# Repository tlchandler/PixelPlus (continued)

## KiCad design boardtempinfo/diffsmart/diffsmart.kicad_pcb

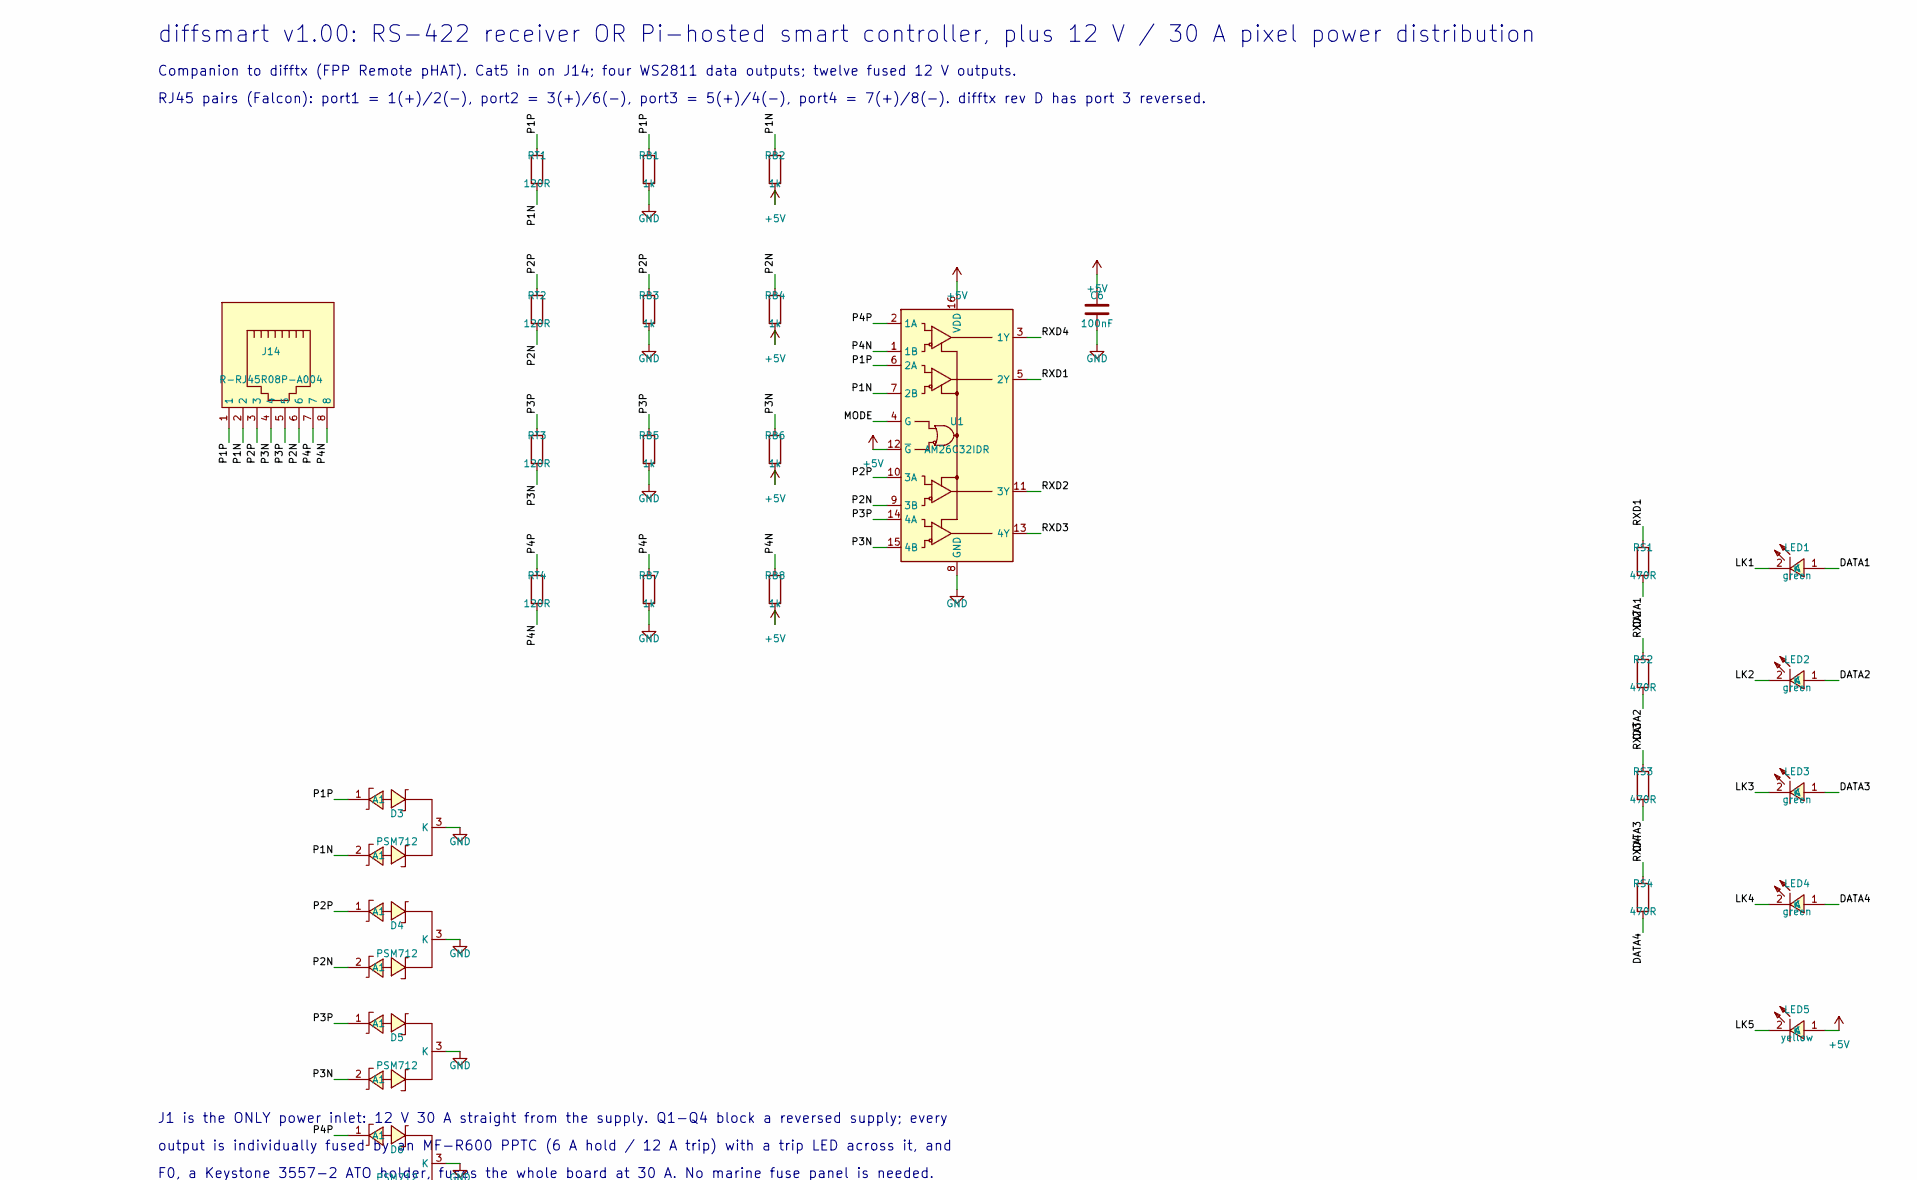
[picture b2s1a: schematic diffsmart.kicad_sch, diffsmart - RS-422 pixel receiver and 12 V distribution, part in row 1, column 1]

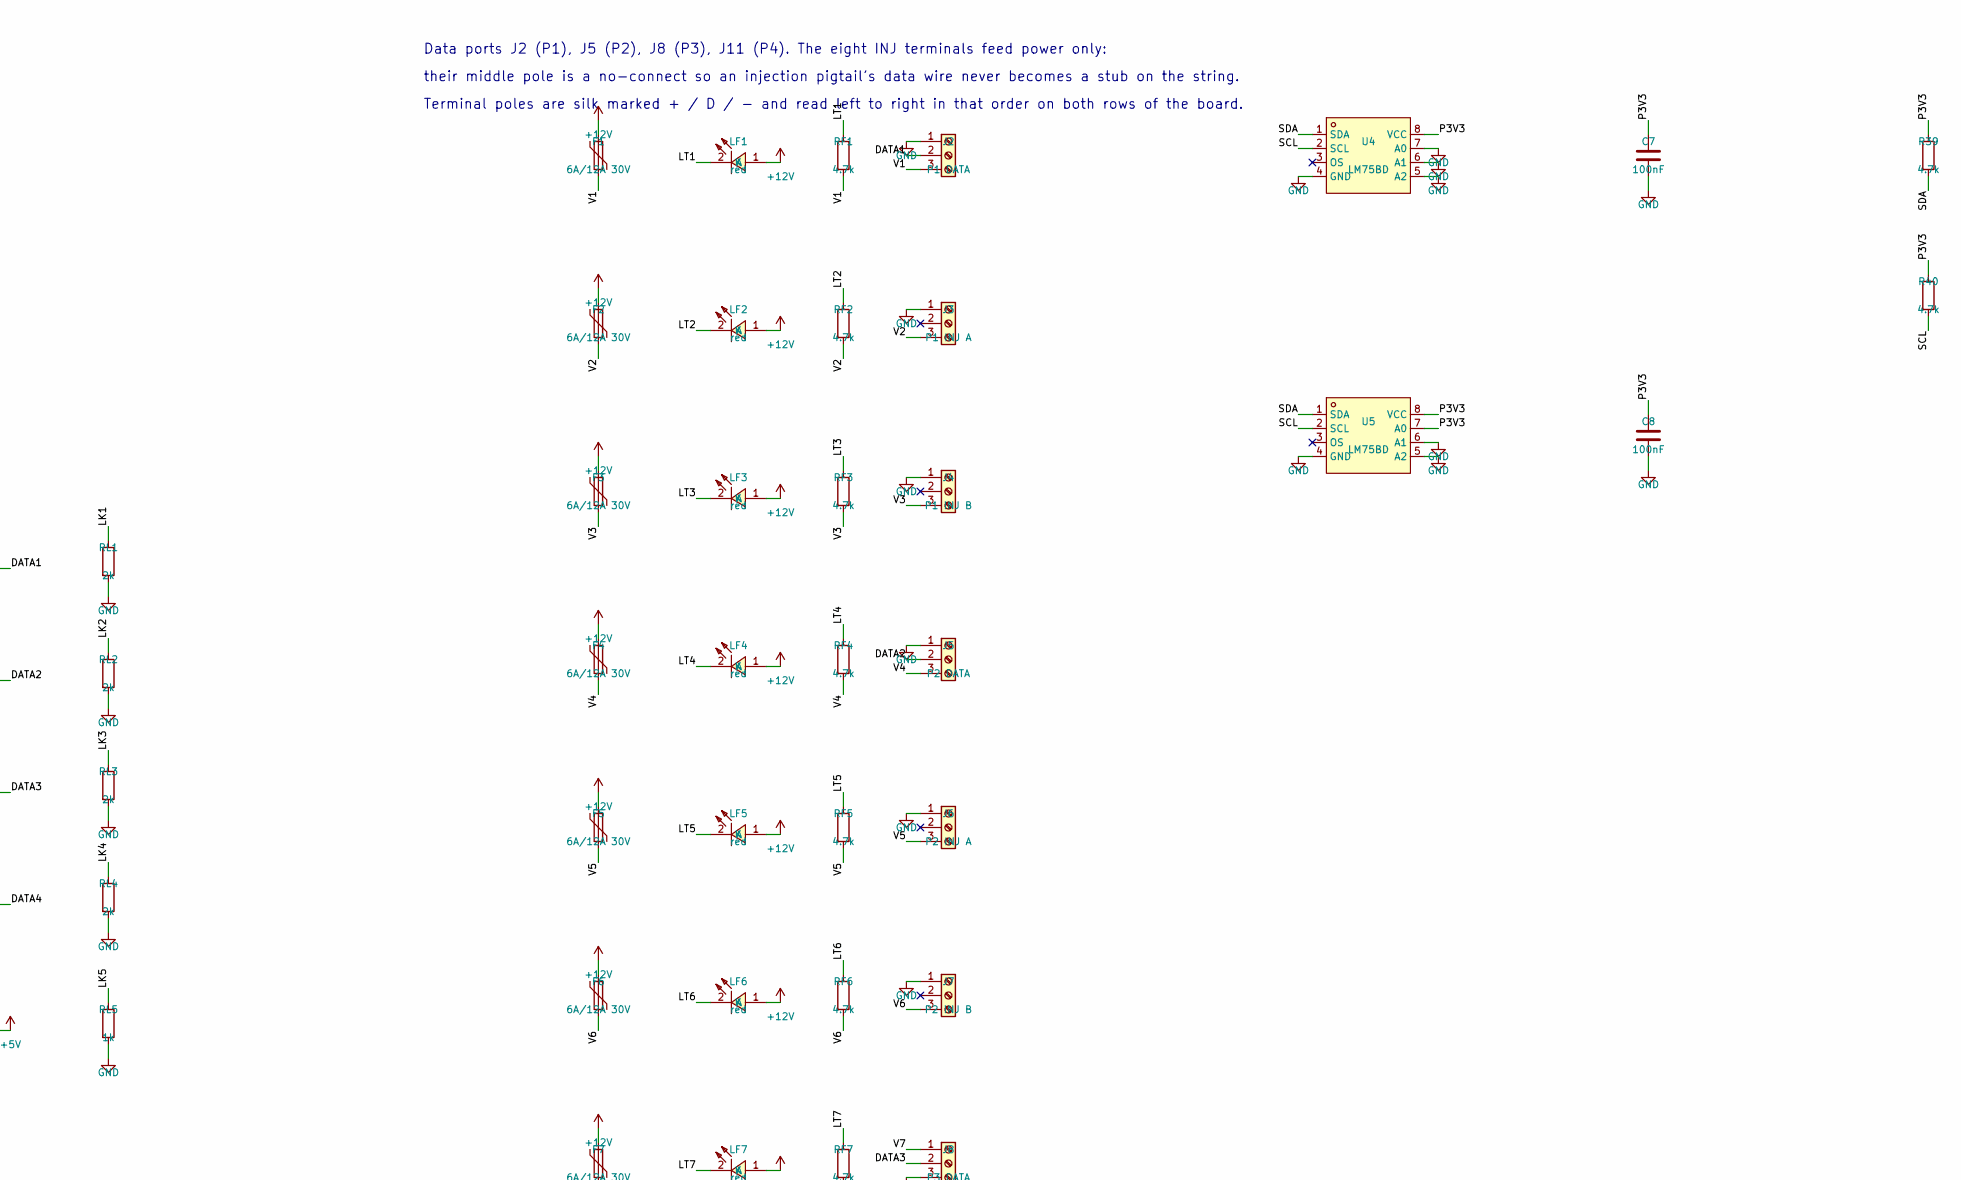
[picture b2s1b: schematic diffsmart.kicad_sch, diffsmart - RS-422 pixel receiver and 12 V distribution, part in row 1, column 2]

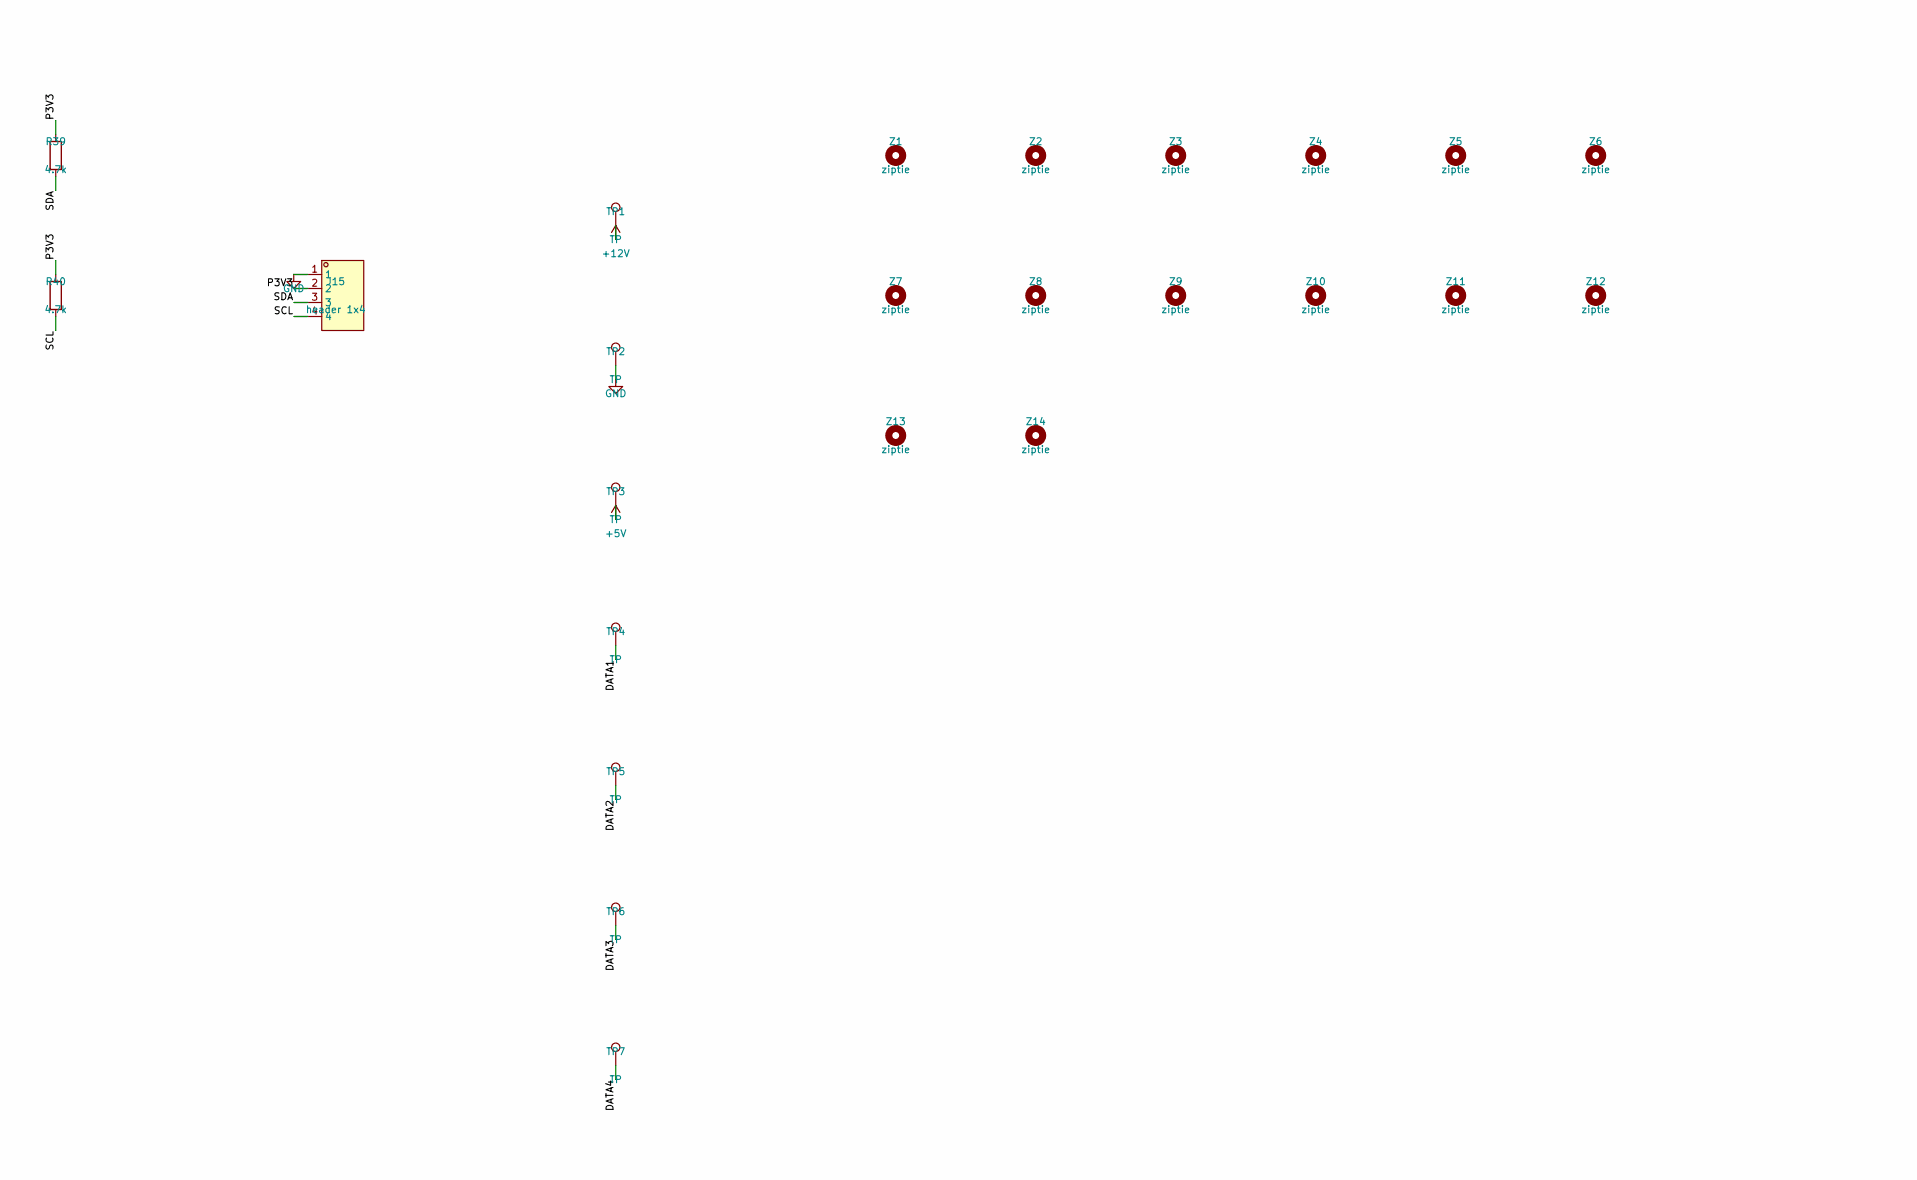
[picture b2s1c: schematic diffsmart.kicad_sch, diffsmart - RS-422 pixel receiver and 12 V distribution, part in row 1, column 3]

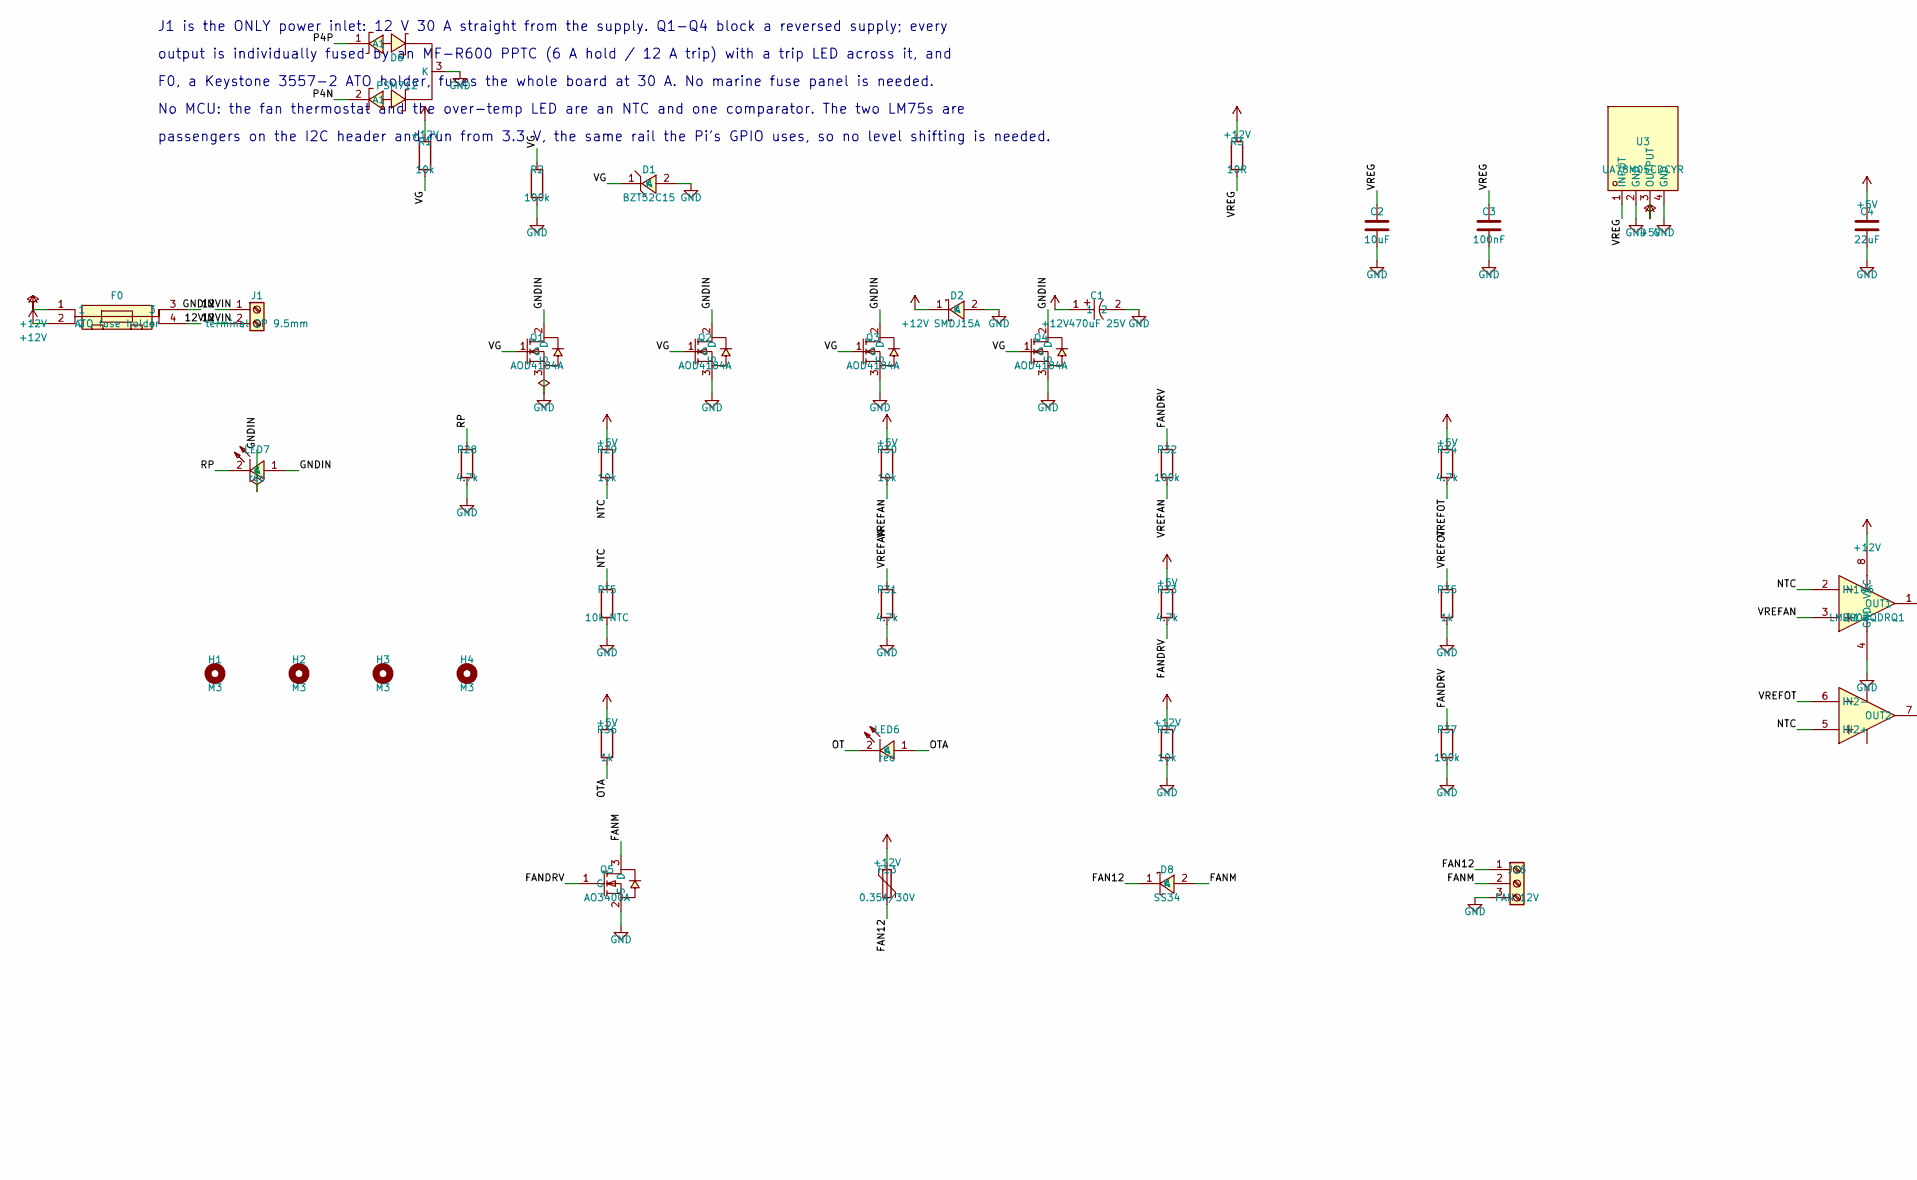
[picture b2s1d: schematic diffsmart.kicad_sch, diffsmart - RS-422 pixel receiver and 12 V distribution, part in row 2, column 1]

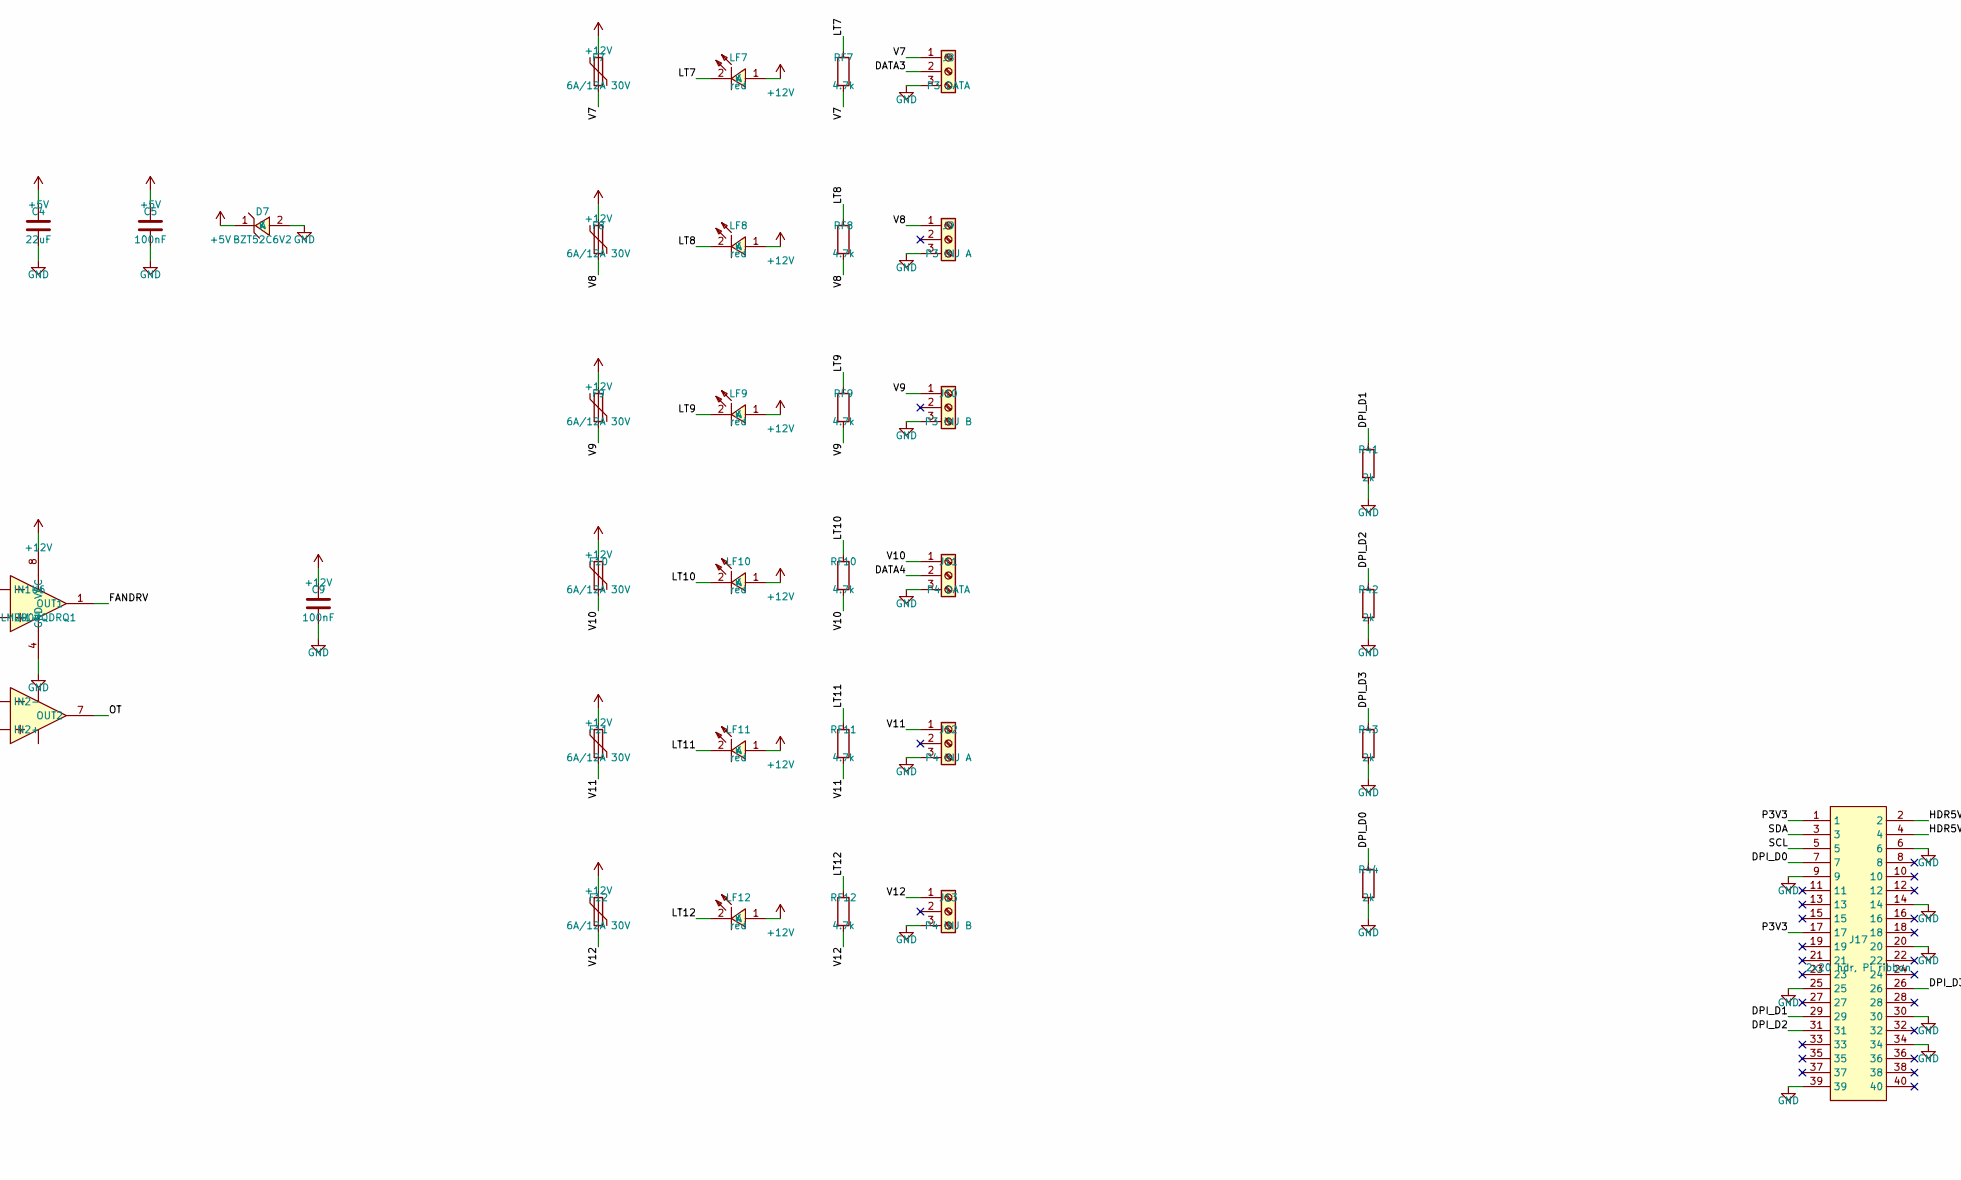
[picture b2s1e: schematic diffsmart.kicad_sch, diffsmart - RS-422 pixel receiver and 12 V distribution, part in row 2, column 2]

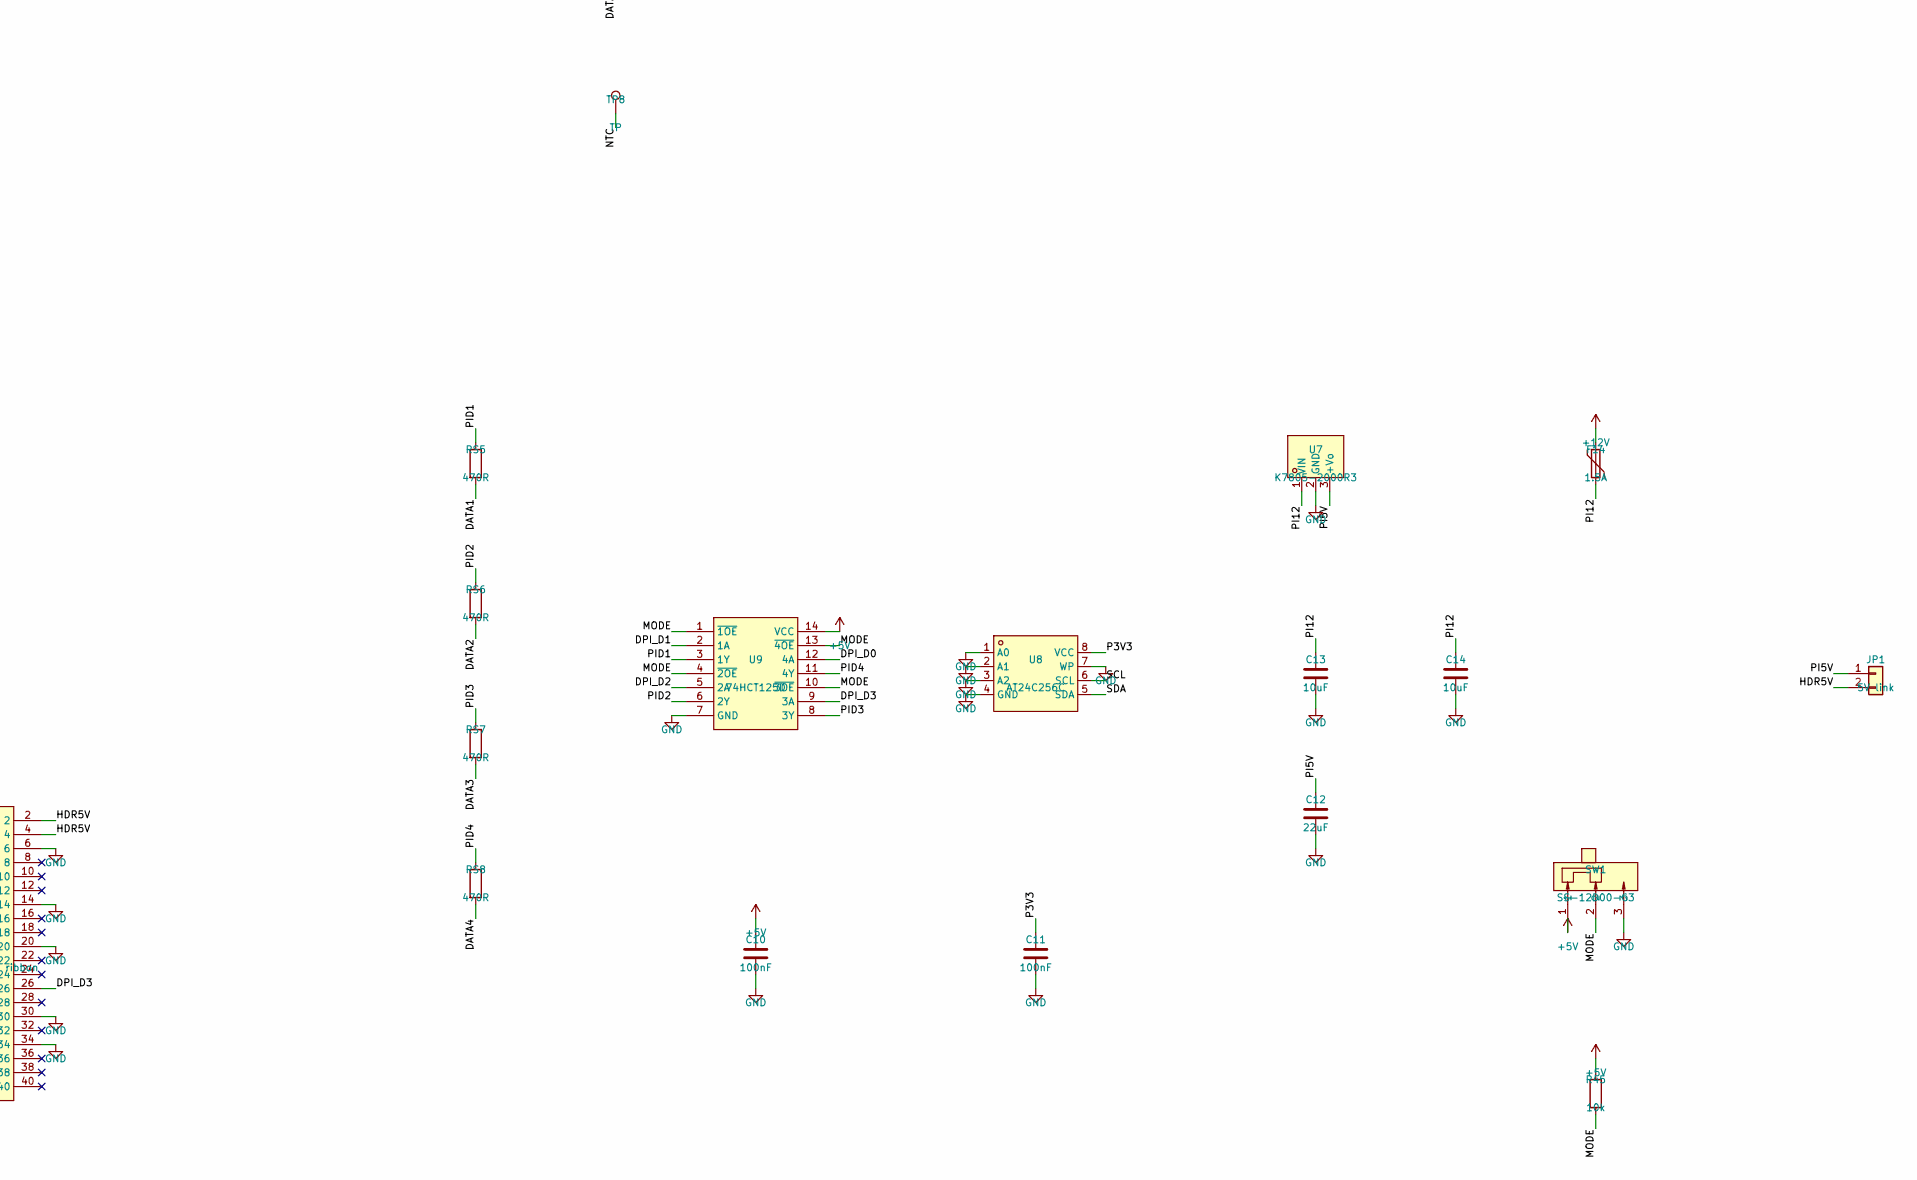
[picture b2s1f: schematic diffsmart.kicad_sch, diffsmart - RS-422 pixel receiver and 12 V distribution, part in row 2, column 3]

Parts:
C1: 470uF 25V; CAP-SMD_BD8.0-L8.3-W8.3-FD; LCSC C4747956
C2, C13, C14: 10uF; C_1206_3216Metric; LCSC C13585
C3, C5, C6, C7, C8, C9, C10, C11: 100nF; C_0805_2012Metric_Pad1.18x1.45mm_HandSolder; LCSC C49678
C4, C12: 22uF; C_0805_2012Metric_Pad1.18x1.45mm_HandSolder; LCSC C45783
D1: BZT52C15; SOD-123_L2.8-W1.8-LS3.7-RD; LCSC C2104
D2: SMDJ15A; SMC_L6.9-W5.9-LS7.9-RD; LCSC C152077
D3, D4, D5, D6: PSM712; SOT-23-3_L3.0-W1.7-P0.95-LS2.9-BR; LCSC C32677
D7: BZT52C6V2; SOD-123_L2.8-W1.8-LS3.7-RD; LCSC C173405
D8: SS34; SMA_L4.3-W2.6-LS5.2-RD; LCSC C8678
F0: ATO fuse holder; FUSE-TH_4P-L19.8-W6.7_3557-2; LCSC C352820
F1, F2, F3, F4, F5, F6, F7, F8, F9, F10, F11, F12: 6A/12A 30V; FUSE-TH_L19.1-W3.0-P10.20-D1.2-S2.0; LCSC C208490
F13: 0.35A/30V; Fuse_1206_3216Metric; LCSC C2876002
F14: 1.5A; F1812; LCSC C22392774
H1, H2, H3, H4: M3; MountingHole_3.2mm_M3
J1: terminal 2P 9.5mm; CONN-TH_P9.50_KF950-9.5-2P; LCSC C475106
J2: P1 DATA; CONN-TH_3P-P5.00_KF301-5.0-3P; LCSC C474882
J3: P1 INJ A; CONN-TH_3P-P5.00_KF301-5.0-3P; LCSC C474882
J4: P1 INJ B; CONN-TH_3P-P5.00_KF301-5.0-3P; LCSC C474882
J5: P2 DATA; CONN-TH_3P-P5.00_KF301-5.0-3P; LCSC C474882
J6: P2 INJ A; CONN-TH_3P-P5.00_KF301-5.0-3P; LCSC C474882
J7: P2 INJ B; CONN-TH_3P-P5.00_KF301-5.0-3P; LCSC C474882
J8: P3 DATA; CONN-TH_3P-P5.00_KF301-5.0-3P; LCSC C474882
J9: P3 INJ A; CONN-TH_3P-P5.00_KF301-5.0-3P; LCSC C474882
J10: P3 INJ B; CONN-TH_3P-P5.00_KF301-5.0-3P; LCSC C474882
J11: P4 DATA; CONN-TH_3P-P5.00_KF301-5.0-3P; LCSC C474882
J12: P4 INJ A; CONN-TH_3P-P5.00_KF301-5.0-3P; LCSC C474882
J13: P4 INJ B; CONN-TH_3P-P5.00_KF301-5.0-3P; LCSC C474882
J14: R-RJ45R08P-A004; RJ45-TH_R-RJ45R08P-A004; LCSC C385834
J15: header 1x4; HDR-TH_4P-P2.54-V-M; LCSC C124378
J16: FAN 12V; CONN-TH_3P-P5.00_KF301-5.0-3P; LCSC C474882
J17: 2x20 hdr, Pi ribbon; PiRibbon_2x20_P2.54mm; LCSC C50980
JP1: 5V link; PinHeader_1x02_P2.54mm_Vertical; LCSC C124375
LED1, LED2, LED3, LED4: green; LED0805-R-RD; LCSC C2297
LED5: yellow; LED0805-R-RD; LCSC C2296
LED6, LED7: red; LED0805-R-RD; LCSC C2295
LF1, LF2, LF3, LF4, LF5, LF6, LF7, LF8, LF9, LF10, LF11, LF12: red; LED0805-R-RD; LCSC C2295
Q1, Q2, Q3, Q4: AOD4184A; TO-252-2_L6.6-W6.1-P4.57-LS9.9-TL-CW; LCSC C99124
Q5: AO3400A; SOT-23-3_L2.9-W1.3-P1.90-LS2.4-BR; LCSC C20917
R1, R27, R29, R30, R45: 10k; R_0603_1608Metric; LCSC C25804
R2, R32, R37: 100k; R_0603_1608Metric; LCSC C25803
R3: 10R; R_0603_1608Metric; LCSC C22859
R28, R31, R33, R34, R39, R40: 4.7k; R_0603_1608Metric; LCSC C23162
R35, R36: 1k; R_0603_1608Metric; LCSC C21190
R41, R42, R43, R44: 2k; R_0603_1608Metric; LCSC C22975
RB1, RB2, RB3, RB4, RB5, RB6, RB7, RB8: 1k; R_0603_1608Metric; LCSC C21190
RF1, RF2, RF3, RF4, RF5, RF6, RF7, RF8, RF9, RF10, RF11, RF12: 4.7k; R_0603_1608Metric; LCSC C23162
RL1, RL2, RL3, RL4: 2k; R_0603_1608Metric; LCSC C22975
RL5: 1k; R_0603_1608Metric; LCSC C21190
RS1, RS2, RS3, RS4, RS5, RS6, RS7, RS8: 470R; R_0603_1608Metric; LCSC C23179
RT1, RT2, RT3, RT4: 120R; R_1206_3216Metric; LCSC C17909
RT5: 10k NTC; R_0805_2012Metric; LCSC C3195213
SW1: SS-12D00-G3; SW-TH_3P-L8.8-W3.9-P2.50_SS12D00G3; LCSC C22355741
TP1, TP2, TP3, TP4, TP5, TP6, TP7, TP8: TP; TestPoint_Pad_D1.5mm
U1: AM26C32IDR; SOIC-16_L9.9-W3.9-P1.27-LS6.0-BL; LCSC C36693
U3: UA78M05CDCYR; SOT-223_L6.5-W3.5-P2.30-LS7.0-BR; LCSC C201654
U4, U5: LM75BD; SOIC-8_L5.0-W4.0-P1.27-LS6.0-BL; LCSC C34565
U6: LM2903QDRQ1; SOIC-8_L4.9-W3.9-P1.27-LS6.0-BL; LCSC C475499
U7: K7805-2000R3; PWRM-TH_K78XX-2000R3; LCSC C18212380
U8: AT24C256C; SOIC-8_L4.9-W3.9-P1.27-LS6.0-BL; LCSC C6482
U9: 74HCT125D; SOIC-14_L8.7-W3.9-P1.27-LS6.0-BL; LCSC C5962
Z1, Z2, Z3, Z4, Z5, Z6, Z7, Z8, Z9, Z10, Z11, Z12, Z13, Z14: ziptie; ZipTie_3.0mm

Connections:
+5V: C4.1, C5.1, C6.1, C10.1, D7.1 (K), LED5.1 (A), R29.1, R30.1, R33.1, R34.1, R36.1, R45.1, RB2.2, RB4.2, RB6.2, RB8.2, SW1.1, TP3.1, U1.12 (~G), U1.16 (VDD), U3.3 (OUTPUT), U9.14 (VCC)
+12V: C1.1, C9.1, D2.1 (K), F0.1, F0.2, F1.1, F2.1, F3.1, F4.1, F5.1, F6.1, F7.1, F8.1, F9.1, F10.1, F11.1, F12.1, F13.1, F14.1, LF1.1 (A), LF2.1 (A), LF3.1 (A), LF4.1 (A), LF5.1 (A), LF6.1 (A), LF7.1 (A), LF8.1 (A), LF9.1 (A), LF10.1 (A), LF11.1 (A), LF12.1 (A), R1.1, R3.1, R27.1, TP1.1, U6.8 (VCC)
/12VIN: F0.3, F0.4, J1.2
/DATA1: J2.2, LED1.1 (A), RS1.2, RS5.2, TP4.1
/DATA2: J5.2, LED2.1 (A), RS2.2, RS6.2, TP5.1
/DATA3: J8.2, LED3.1 (A), RS3.2, RS7.2, TP6.1
/DATA4: J11.2, LED4.1 (A), RS4.2, RS8.2, TP7.1
/DPI_D0: J17.7, R44.1, U9.12 (4A)
/DPI_D1: J17.29, R41.1, U9.2 (1A)
/DPI_D2: J17.31, R42.1, U9.5 (2A)
/DPI_D3: J17.26, R43.1, U9.9 (3A)
/FAN12: D8.1 (K), F13.2, J16.1
/FANDRV: Q5.1 (G), R32.1, R33.2, R37.1, U6.1 (OUT1)
/FANM: D8.2 (A), J16.2, Q5.3 (D)
/GNDIN: J1.1, LED7.1 (A), Q1.2 (D), Q2.2 (D), Q3.2 (D), Q4.2 (D)
/HDR5V: J17.2, J17.4, JP1.2
/LK1: LED1.2 (K), RL1.1
/LK2: LED2.2 (K), RL2.1
/LK3: LED3.2 (K), RL3.1
/LK4: LED4.2 (K), RL4.1
/LK5: LED5.2 (K), RL5.1
/LT1: LF1.2 (K), RF1.1
/LT2: LF2.2 (K), RF2.1
/LT3: LF3.2 (K), RF3.1
/LT4: LF4.2 (K), RF4.1
/LT5: LF5.2 (K), RF5.1
/LT6: LF6.2 (K), RF6.1
/LT7: LF7.2 (K), RF7.1
/LT8: LF8.2 (K), RF8.1
/LT9: LF9.2 (K), RF9.1
/LT10: LF10.2 (K), RF10.1
/LT11: LF11.2 (K), RF11.1
/LT12: LF12.2 (K), RF12.1
/MODE: R45.2, SW1.2, U1.4 (G), U9.1 (~1OE), U9.4 (~2OE), U9.10 (~3OE), U9.13 (~4OE)
/NTC: R29.2, RT5.1, TP8.1, U6.2 (IN1-), U6.5 (IN2+)
/OT: LED6.2 (K), U6.7 (OUT2)
/OTA: LED6.1 (A), R36.2
/P1N: D3.2 (A1), J14.2, RB2.1, RT1.2, U1.7 (2B)
/P1P: D3.1 (A1), J14.1, RB1.1, RT1.1, U1.6 (2A)
/P2N: D4.2 (A1), J14.6, RB4.1, RT2.2, U1.9 (3B)
/P2P: D4.1 (A1), J14.3, RB3.1, RT2.1, U1.10 (3A)
/P3N: D5.2 (A1), J14.4, RB6.1, RT3.2, U1.15 (4B)
/P3P: D5.1 (A1), J14.5, RB5.1, RT3.1, U1.14 (4A)
/P3V3: C7.1, C8.1, C11.1, J15.2, J17.1, J17.17, R39.1, R40.1, U4.8 (VCC), U5.7 (A0), U5.8 (VCC), U8.8 (VCC)
/P4N: D6.2 (A1), J14.8, RB8.1, RT4.2, U1.1 (1B)
/P4P: D6.1 (A1), J14.7, RB7.1, RT4.1, U1.2 (1A)
/PI5V: C12.1, JP1.1, U7.3 (+Vo)
/PI12: C13.1, C14.1, F14.2, U7.1 (VIN)
/PID1: RS5.1, U9.3 (1Y)
/PID2: RS6.1, U9.6 (2Y)
/PID3: RS7.1, U9.8 (3Y)
/PID4: RS8.1, U9.11 (4Y)
/RP: LED7.2 (K), R28.1
/RXD1: RS1.1, U1.5 (2Y)
/RXD2: RS2.1, U1.11 (3Y)
/RXD3: RS3.1, U1.13 (4Y)
/RXD4: RS4.1, U1.3 (1Y)
/SCL: J15.4, J17.5, R40.2, U4.2 (SCL), U5.2 (SCL), U8.6 (SCL)
/SDA: J15.3, J17.3, R39.2, U4.1 (SDA), U5.1 (SDA), U8.5 (SDA)
/V1: F1.2, J2.3, RF1.2
/V2: F2.2, J3.3, RF2.2
/V3: F3.2, J4.3, RF3.2
/V4: F4.2, J5.3, RF4.2
/V5: F5.2, J6.3, RF5.2
/V6: F6.2, J7.3, RF6.2
/V7: F7.2, J8.1, RF7.2
/V8: F8.2, J9.1, RF8.2
/V9: F9.2, J10.1, RF9.2
/V10: F10.2, J11.1, RF10.2
/V11: F11.2, J12.1, RF11.2
/V12: F12.2, J13.1, RF12.2
/VG: D1.1 (K), Q1.1 (G), Q2.1 (G), Q3.1 (G), Q4.1 (G), R1.2, R2.1
/VREFAN: R30.2, R31.1, R32.2, U6.3 (IN1+)
/VREFOT: R34.2, R35.1, U6.6 (IN2-)
/VREG: C2.1, C3.1, R3.2, U3.1 (INPUT)
GND: C1.2, C2.2, C3.2, C4.2, C5.2, C6.2, C7.2, C8.2, C9.2, C10.2, C11.2, C12.2, C13.2, C14.2, D1.2 (A), D2.2 (A), D3.3 (K), D4.3 (K), D5.3 (K), D6.3 (K), D7.2 (A), J2.1, J3.1, J4.1, J5.1, J6.1, J7.1, J8.3, J9.3, J10.3, J11.3, J12.3, J13.3, J15.1, J16.3, J17.6, J17.9, J17.14, J17.20, J17.25, J17.30, J17.34, J17.39, Q1.3 (S), Q2.3 (S), Q3.3 (S), Q4.3 (S), Q5.2 (S), R2.2, R27.2, R28.2, R31.2, R35.2, R37.2, R41.2, R42.2, R43.2, R44.2, RB1.2, RB3.2, RB5.2, RB7.2, RL1.2, RL2.2, RL3.2, RL4.2, RL5.2, RT5.2, SW1.3, TP2.1, U1.8 (GND), U3.2 (GND), U3.4 (GND), U4.4 (GND), U4.5 (A2), U4.6 (A1), U4.7 (A0), U5.4 (GND), U5.5 (A2), U5.6 (A1), U6.4 (GND), U7.2 (GND), U8.1 (A0), U8.2 (A1), U8.3 (A2), U8.4 (GND), U8.7 (WP), U9.7 (GND)

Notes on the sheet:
diffsmart v1.00: RS-422 receiver OR Pi-hosted smart controller, plus 12 V / 30 A pixel power distribution
Companion to difftx (FPP Remote pHAT). Cat5 in on J14; four WS2811 data outputs; twelve fused 12 V outputs.
RJ45 pairs (Falcon): port1 = 1(+)/2(-), port2 = 3(+)/6(-), port3 = 5(+)/4(-), port4 = 7(+)/8(-). difftx rev D has port 3 reversed.
J1 is the ONLY power inlet: 12 V 30 A straight from the supply. Q1-Q4 block a reversed supply; every
output is individually fused by an MF-R600 PPTC (6 A hold / 12 A trip) with a trip LED across it, and
F0, a Keystone 3557-2 ATO holder, fuses the whole board at 30 A. No marine fuse panel is needed.
No MCU: the fan thermostat and the over-temp LED are an NTC and one comparator. The two LM75s are
passengers on the I2C header and run from 3.3 V, the same rail the Pi's GPIO uses, so no level shifting is needed.
Data ports J2 (P1), J5 (P2), J8 (P3), J11 (P4). The eight INJ terminals feed power only:
their middle pole is a no-connect so an injection pigtail's data wire never becomes a stub on the string.
Terminal poles are silk marked + / D / - and read left to right in that order on both rows of the board.

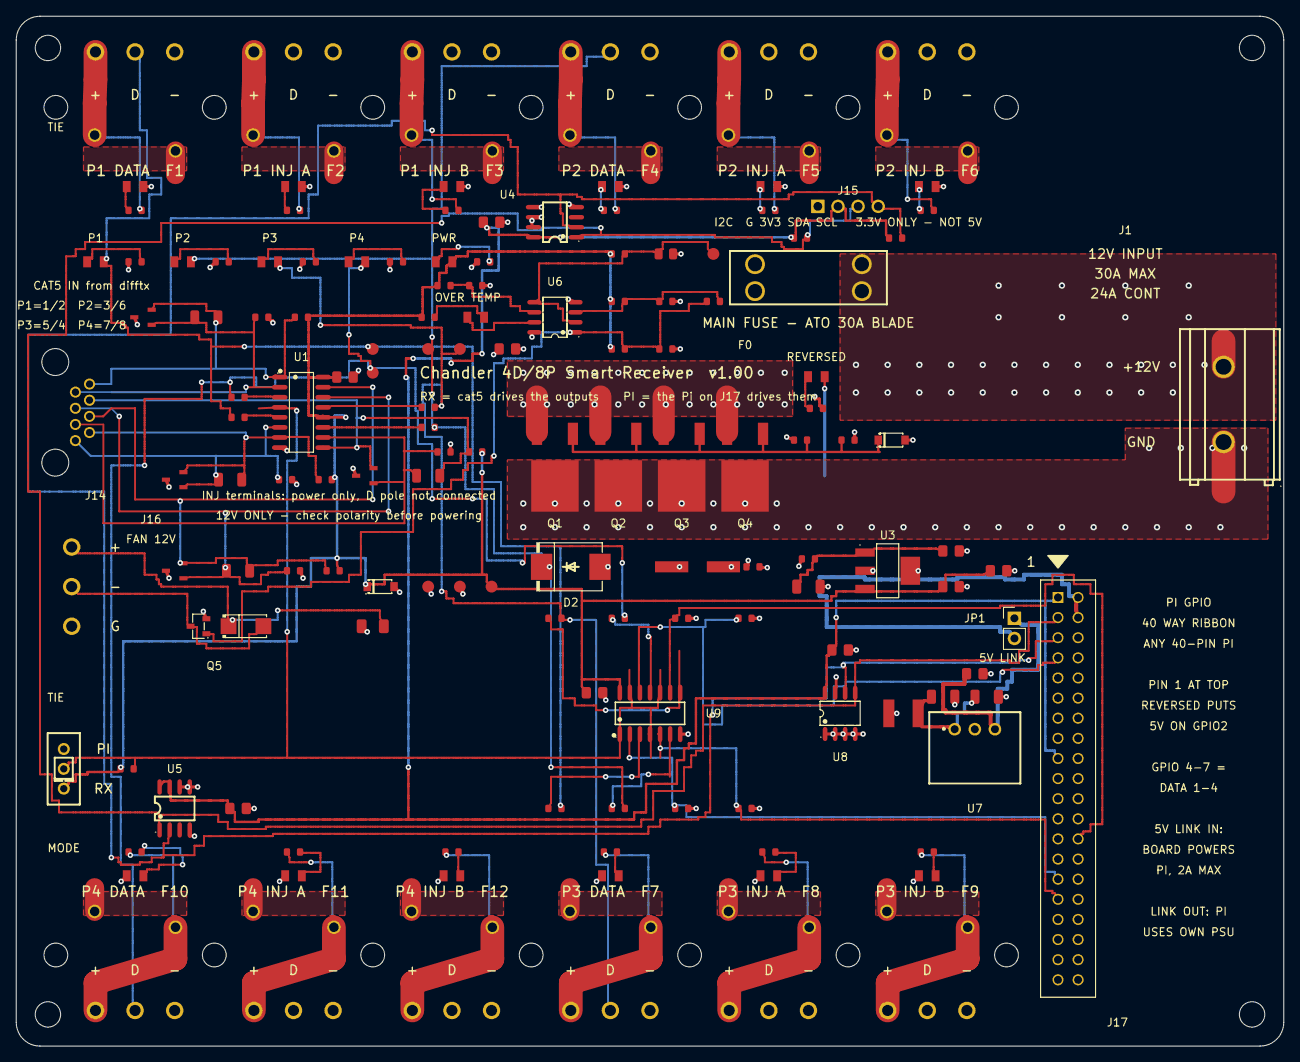
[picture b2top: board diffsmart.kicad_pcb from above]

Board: 4 copper layers, 160.0 x 130.0 mm, 173 parts (0 on the bottom side), 76 nets.
